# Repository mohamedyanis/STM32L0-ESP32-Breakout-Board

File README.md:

# STM32L0-ESP32 Breakout Board

This is a small breakout Printed Circuit Board (PCB) that is based on the STM32 microcontroller as well as the ESP32 dev module.
The PCB is designed using the free and open source software <a href="https://github.com/KiCad">KiCad</a>. 

## More Details
The PCB is based on the STM32L0 series, specifically the STM32L031G6U6 microcontroller which is a low power based MCU. The MCU is operated with a High Speed Internal (HSI) clock signal of a 16 MHz crystal oscillator (No external quartz is needed).<br><br>
It's operating with an input voltage from 12V to 5V. The input voltage will be filtered and reduced to 3V3 in order to power the STM32 MCU as well as the ESP32 module.<br><br>
The purpose of this PCB is to control the temperature with a PID controller. It has two connectors for that, one for reading temperature value with a thermostat, a thermocouple, or a temperature IC (LM36/LM35) that gives an analog signal, and the other connector is used to control the temperature using a Solid State Relay (SSR) controlled by a PWM signal.<br><br>
The data read from the STM32 MCU is transmitted to the ESP32 dev module via 'USART' protocol in order to send the data to the cloud and the temperature could be controlled wirelessly anywhere with a smart phone or a web application.<br><br>
STM32 MCU can be flashed using SWD programmer and the ESP32 dev module could be programmed using a USB-to-TTL converter.<br><br>

## Features :dart:
* [x] Four layers PCB
* [x] Low power
* [x] Small size
* [x] Very easy to use

## Thank _You_!
Please :star: this repo to help us improve the quality.
<br><br>

## PCB Block Diagram
PCB System Block
:---------------------:

## 3D Viewer
Front View           | Back View
:---------------------:|:------------------:
 | 
Side View 1         |  Side View 2
 | 
Side View 3         |  Side View 4
 | 

## Requirements

If you want to review the PCB or yoou wanna edit the schematics/layout, you only need to install KiCad software to your machine.

* Go to the <a href="https://www.kicad.org/download/">Official KiCad Download Page</a>.
* Select your operating system.
* Download the executable file and install it.

## Documentations
Open the [Datasheets](Datasheets) folder and you will find all the datasheets, applications notes, and design guidelines that help you understand the design better.

## How To Use It

1. Install this repository, click <a href="https://github.com/mohamedyanis/STM32L0-ESP32-Breakout-Board/archive/master.zip"> here </a> to install it. Or use git command:
```bach
git clone https://github.com/mohamedyanis/STM32L0-ESP32-Breakout-Board.git
```
2. Extract the folder and open it.
3. Navigate for the [Manufacturing](Manufacturing) folder.
4. Go to your best PCB manufacturer website and click on quote.
5. Upload the [STM32L0-ESP32-Breakout-Board-Gerber.rar](Manufacturing/Gerber/STM32L0-ESP32-Breakout-Board-Gerber.rar) in order to order the board.
6. In case you want to receive it assembled, upload the [STM32L0_ESP32_Breakout_Board_BOM.csv](Manufacturing/Assembly/STM32L0_ESP32_Breakout_Board_BOM.csv) and [STM32L0_ESP32_Breakout_Board_Components_Positions.csv](Manufacturing/Assembly/STM32L0_ESP32_Breakout_Board_Components_Positions.csv) files.

## License
The content of this project is licenced under the [BSD 3-Clause "New" or "Revised" License](LICENSE).

## Contributing 💡
If you want to contribute to this project and make it better with new ideas, your pull request is very welcomed.<br>
If you find any issue just put it in the repository issue section, thanks!<br><br>
.سبحَانَكَ اللَّهُمَّ وَبِحَمْدِكَ، أَشْهَدُ أَنْ لا إِلهَ إِلأَ انْتَ أَسْتَغْفِرُكَ وَأَتْوبُ إِلَيْكَ

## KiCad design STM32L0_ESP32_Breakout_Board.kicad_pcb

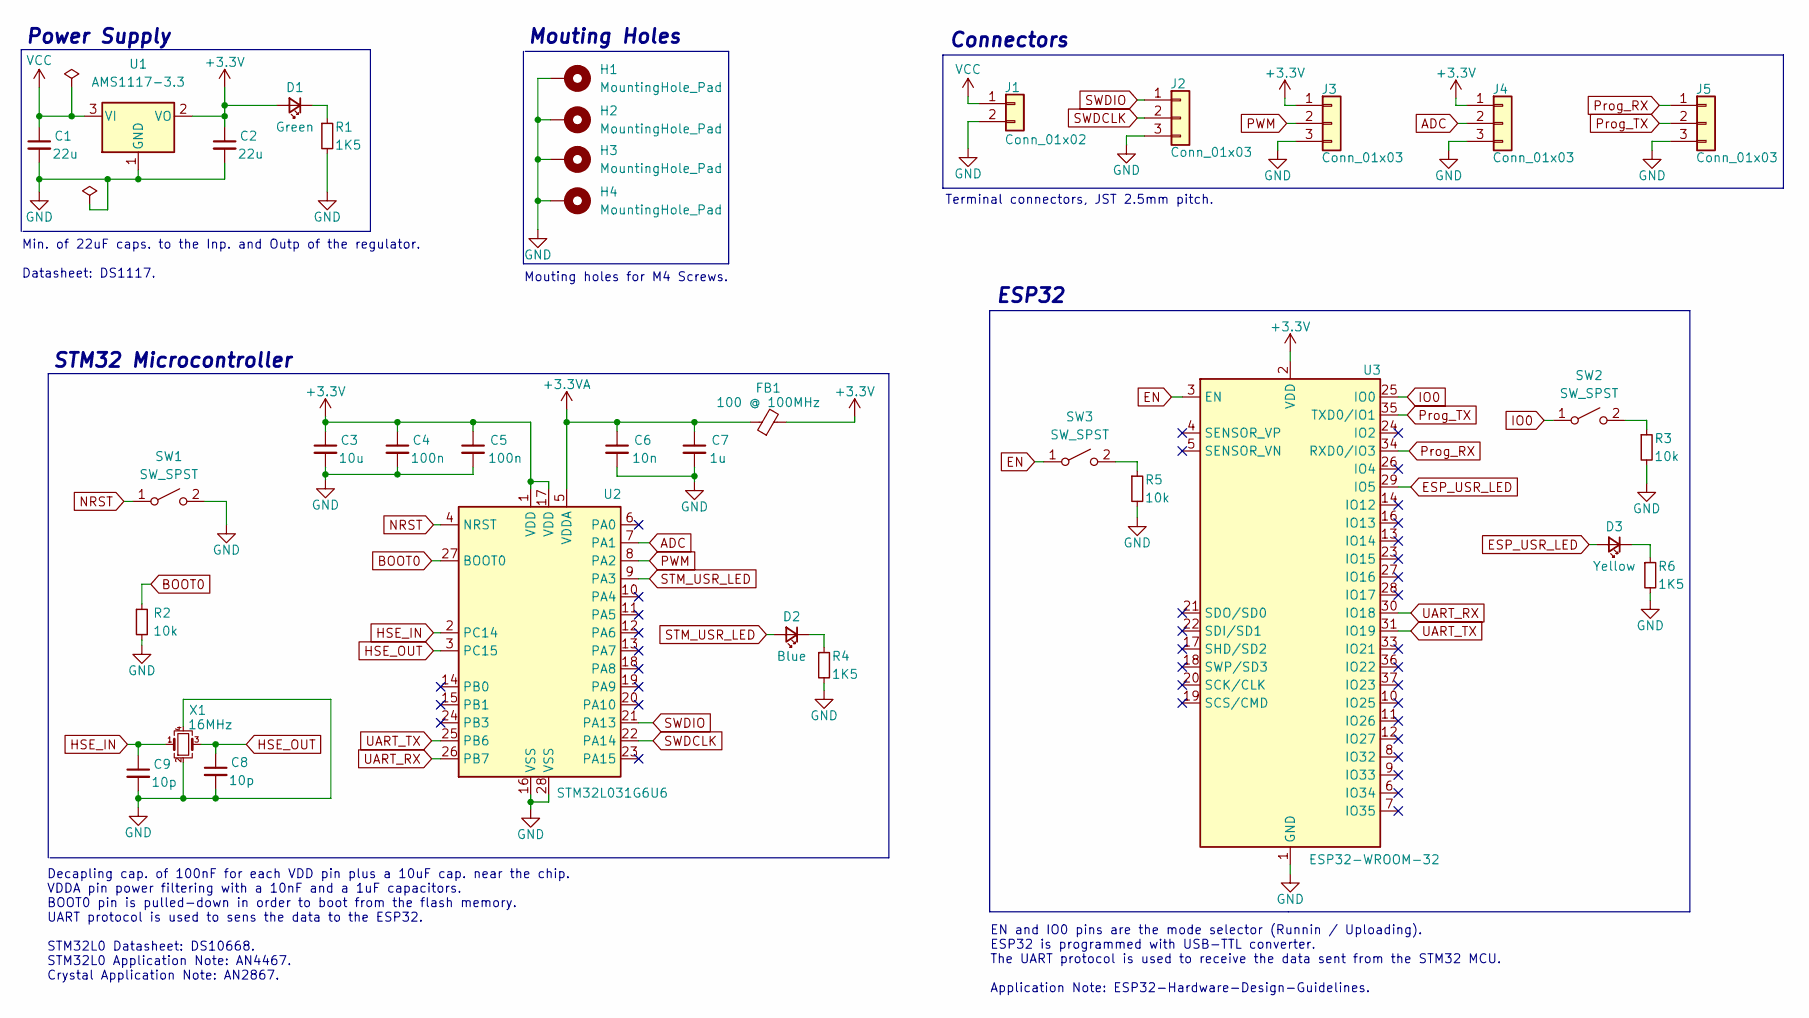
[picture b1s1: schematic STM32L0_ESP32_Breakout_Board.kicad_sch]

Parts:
C1, C2: 22u; C_0603_1608Metric
C3: 10u; C_0402_1005Metric
C4, C5: 100n; C_0402_1005Metric
C6: 10n; C_0402_1005Metric
C7: 1u; C_0402_1005Metric
C8, C9: 10p; C_0402_1005Metric
D1: Green; LED_0603_1608Metric
D2: Blue; LED_0603_1608Metric
D3: Yellow; LED_0603_1608Metric
FB1: 100 @ 100MHz; L_0402_1005Metric
H1, H2, H3, H4: MountingHole_Pad; MountingHole_4.3mm_M4_Pad_Via
J1: Conn_01x02; JST_XH_S2B-XH-A_1x02_P2.50mm_Horizontal
J2, J3, J4, J5: Conn_01x03; JST_XH_S3B-XH-A_1x03_P2.50mm_Horizontal
R1, R4, R6: 1K5; R_0402_1005Metric
R2, R3, R5: 10k; R_0402_1005Metric
SW1, SW2, SW3: SW_SPST; SW_SPST_B3U-1000P
U1: AMS1117-3.3; SOT-223-3_TabPin2
U2: STM32L031G6U6; QFN-28_4x4mm_P0.5mm
U3: ESP32-WROOM-32
X1: 16MHz; Crystal_SMD_SeikoEpson_TSX3225-4Pin_3.2x2.5mm

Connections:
+3.3V: C2.1, C3.1, C4.1, C5.1, D1.2 (A), FB1.2, J3.1, J4.1, U1.2 (VO), U2.1 (VDD), U2.17 (VDD), U3.2 (VDD)
+3.3VA: C6.1, C7.1, FB1.1, U2.5 (VDDA)
ADC: J4.2, U2.7 (PA1)
BOOT0: R2.1, U2.27 (BOOT0)
EN: SW3.1 (A), U3.3 (EN)
ESP_USR_LED: D3.2 (A), U3.29 (IO5)
GND: C1.2, C2.2, C3.2, C4.2, C5.2, C6.2, C7.2, C8.2, C9.2, H1.1, H2.1, H3.1, H4.1, J1.2, J2.3, J3.3, J4.3, J5.3, R1.2, R2.2, R3.2, R4.2, R5.2, R6.2, SW1.2 (B), U1.1 (GND), U2.16 (VSS), U2.28 (VSS), U3.1 (GND), U3.15 (GND), U3.38 (GND), U3.39 (GND), X1.2, X1.4
HSE_IN: C9.1, U2.2 (PC14), X1.1
HSE_OUT: C8.1, U2.3 (PC15), X1.3
IO0: SW2.1 (A), U3.25 (IO0)
NRST: SW1.1 (A), U2.4 (NRST)
unnamed: D1.1 (K), R1.1
unnamed: D2.1 (K), R4.1
unnamed: D3.1 (K), R6.1
unnamed: R3.1, SW2.2 (B)
unnamed: R5.1, SW3.2 (B)
PWM: J3.2, U2.8 (PA2)
Prog_RX: J5.1, U3.34 (RXD0/IO3)
Prog_TX: J5.2, U3.35 (TXD0/IO1)
STM_USR_LED: D2.2 (A), U2.9 (PA3)
SWDCLK: J2.2, U2.22 (PA14)
SWDIO: J2.1, U2.21 (PA13)
UART_RX: U2.26 (PB7), U3.30 (IO18)
UART_TX: U2.25 (PB6), U3.31 (IO19)
VCC: C1.1, J1.1, U1.3 (VI)

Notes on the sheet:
Min. of 22uF caps. to the Inp. and Outp of the regulator. Datasheet: DS1117.
Terminal connectors, JST 2.5mm pitch.
Power Supply
Mouting Holes
Connectors
STM32 Microcontroller
Decapling cap. of 100nF for each VDD pin plus a 10uF cap. near the chip. VDDA pin power filtering with a 10nF and a 1uF capacitors. BOOT0 pin is pulled-down in order to boot from the flash memory. UART protocol is used to sens the data to the ESP32. STM32L0 Datasheet: DS10668. STM32L0 Application N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
EN and IO0 pins are the mode selector (Runnin / Uploading). ESP32 is programmed with USB-TTL converter. The UART protocol is used to receive the data sent from the STM32 MCU. Application Note: ESP32-Hardware-Design-Guidelines.
ESP32
Mouting holes for M4 Screws.

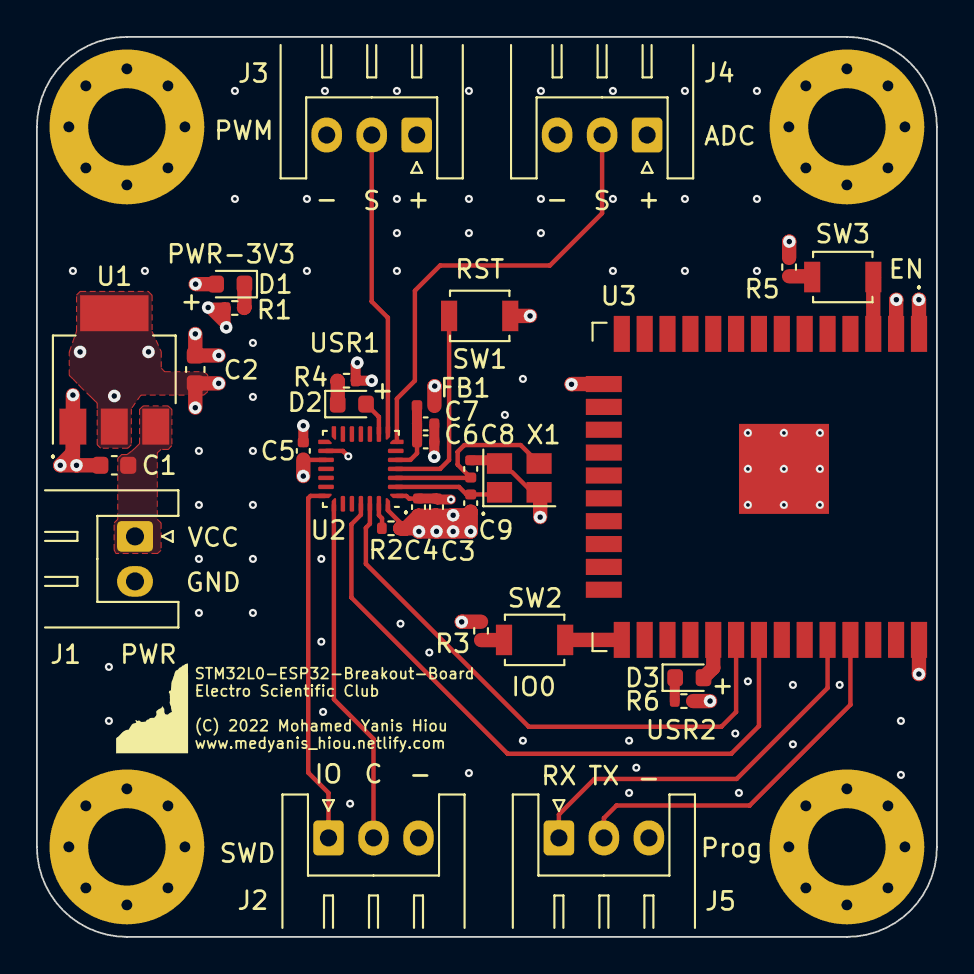
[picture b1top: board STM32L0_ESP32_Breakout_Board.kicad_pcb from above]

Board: 4 copper layers, 50.0 x 50.0 mm, 35 parts (0 on the bottom side), 25 nets.

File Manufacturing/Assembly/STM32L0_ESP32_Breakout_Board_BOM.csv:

Designator,Quantity,Value,Footprint,LCSC Part #,Type
"C1, C2, ",2,22u,C_0603_1608Metric,C59461,SMD
"C3, ",1,10u,C_0402_1005Metric,C15525,SMD
"C4, C5, ",2,100n,C_0402_1005Metric,C1525,SMD
"C6, ",1,10n,C_0402_1005Metric,C15195,SMD
"C7, ",1,1u,C_0402_1005Metric,C52923,SMD
"C8, C9, ",2,10p,C_0402_1005Metric,C32949,DNP
"D1, ",1,Green,LED_0603_1608Metric,C72043,SMD
"D2, ",1,Blue,LED_0603_1608Metric,C72041,SMD
"D3, ",1,Yellow,LED_0603_1608Metric,C72038,SMD
"FB1, ",1,100 @ 100MHz,L_0402_1005Metric,C85817,SMD
"R1, R4, R6, ",3,1K5,R_0402_1005Metric,C279987,SMD
"R2, R3, R5, ",3,10k,R_0402_1005Metric,C409612,SMD
"SW1, SW2, SW3, ",3,SW_SPST,SW_SPST_B3U-1000P,C231329,SMD
"U1, ",1,AMS1117-3.3,SOT-223-3,C6186,SMD
"U2, ",1,STM32L031G6U6,QFN-28_4x4mm,C96514,SMD
"U3, ",1,ESP32-WROOM-32,ESP32-WROOM-32,C529582,SMD
"X1, ",1,16MHz,Crystal_SMD_TSX3225,C13738,DNP

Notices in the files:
README.md:
License: BSD 3-Clause
STM32L0_ESP32_Breakout_Board.kicad_pcb:
(C) 2022 Mohamed Yanis Hiou
